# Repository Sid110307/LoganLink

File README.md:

# LoganLink

> Connected-Vehicle System for OBD-II supported cars

An OBD-II dongle plus a native Android app for older OBD-II petrol cars. The dongle reads the engine ECU over the K-line
(ISO 9141-2 / ISO 14230 KWP2000), measures the 12 V system (battery, cranking, charging), records driving events with an
accelerometer, logs locally and streams to the phone over Bluetooth LE. The phone supplies GPS, UI, trip history and alerts.

Developed on a 2008 Renault X90-platform sedan with the K7M 1.6.

## Repository

| Path | Contents |
| ------ | ---------- |
| `firmware/` | ESP-IDF v5.3 C firmware |
| `android/` | Android app |
| `hardware/` | PCB and BOM |
| `mechanical/` | Enclosure and print stuff |

## Features

- [x] QR card pairing with the dongle
- [x] Owner + up to 3 drivers with roles
- [x] Live RPM, speed, coolant, MAP, throttle, load, trims, battery, etc.
- [x] Full-screen Drive Mode
- [x] Floating car panel over Maps
- [x] Route map for every trip
- [x] Driving score from harsh braking, acceleration and idling
- [x] Trip summary notifications
- [x] Fuel consumption that self-calibrates with each fill-up
- [x] Fuel log and cost history
- [x] Alerts for overheating, charging faults, overvoltage, etc.
- [x] Charging system check
- [x] Battery health from cranking voltage
- [x] Service reminders by km and time
- [x] Odometer kept up to date by trips
- [x] VIN read and decoded (maker, model year)
- [x] Automatic protocol detection for K-line cars
- [x] Battery voltage calibration
- [x] Offline dongle logging
- [x] GPS speed when the car doesn't report it
- [x] RPM from alternator ripple fallback
- [x] Firmware updates over BT
- [x] Status LED for standby and driving
- [x] Low-power parked mode with hibernation
- [ ] Manufacturer data blocks for older ECUs
- [ ] Fuel level
- [ ] Ignition sensing
- [ ] Multiple cars in one app
- [ ] Home-screen widgets for battery, fuel and last trip
- [ ] "Where is my car" with Google Assistant
- [ ] Freeze frame data for fault codes
- [ ] Idle and fuel-trim adaptation resets
- [ ] Actuator tests: fan, fuel pump, A/C clutch, injectors
- [ ] Android Auto status cards
- [ ] CAN support

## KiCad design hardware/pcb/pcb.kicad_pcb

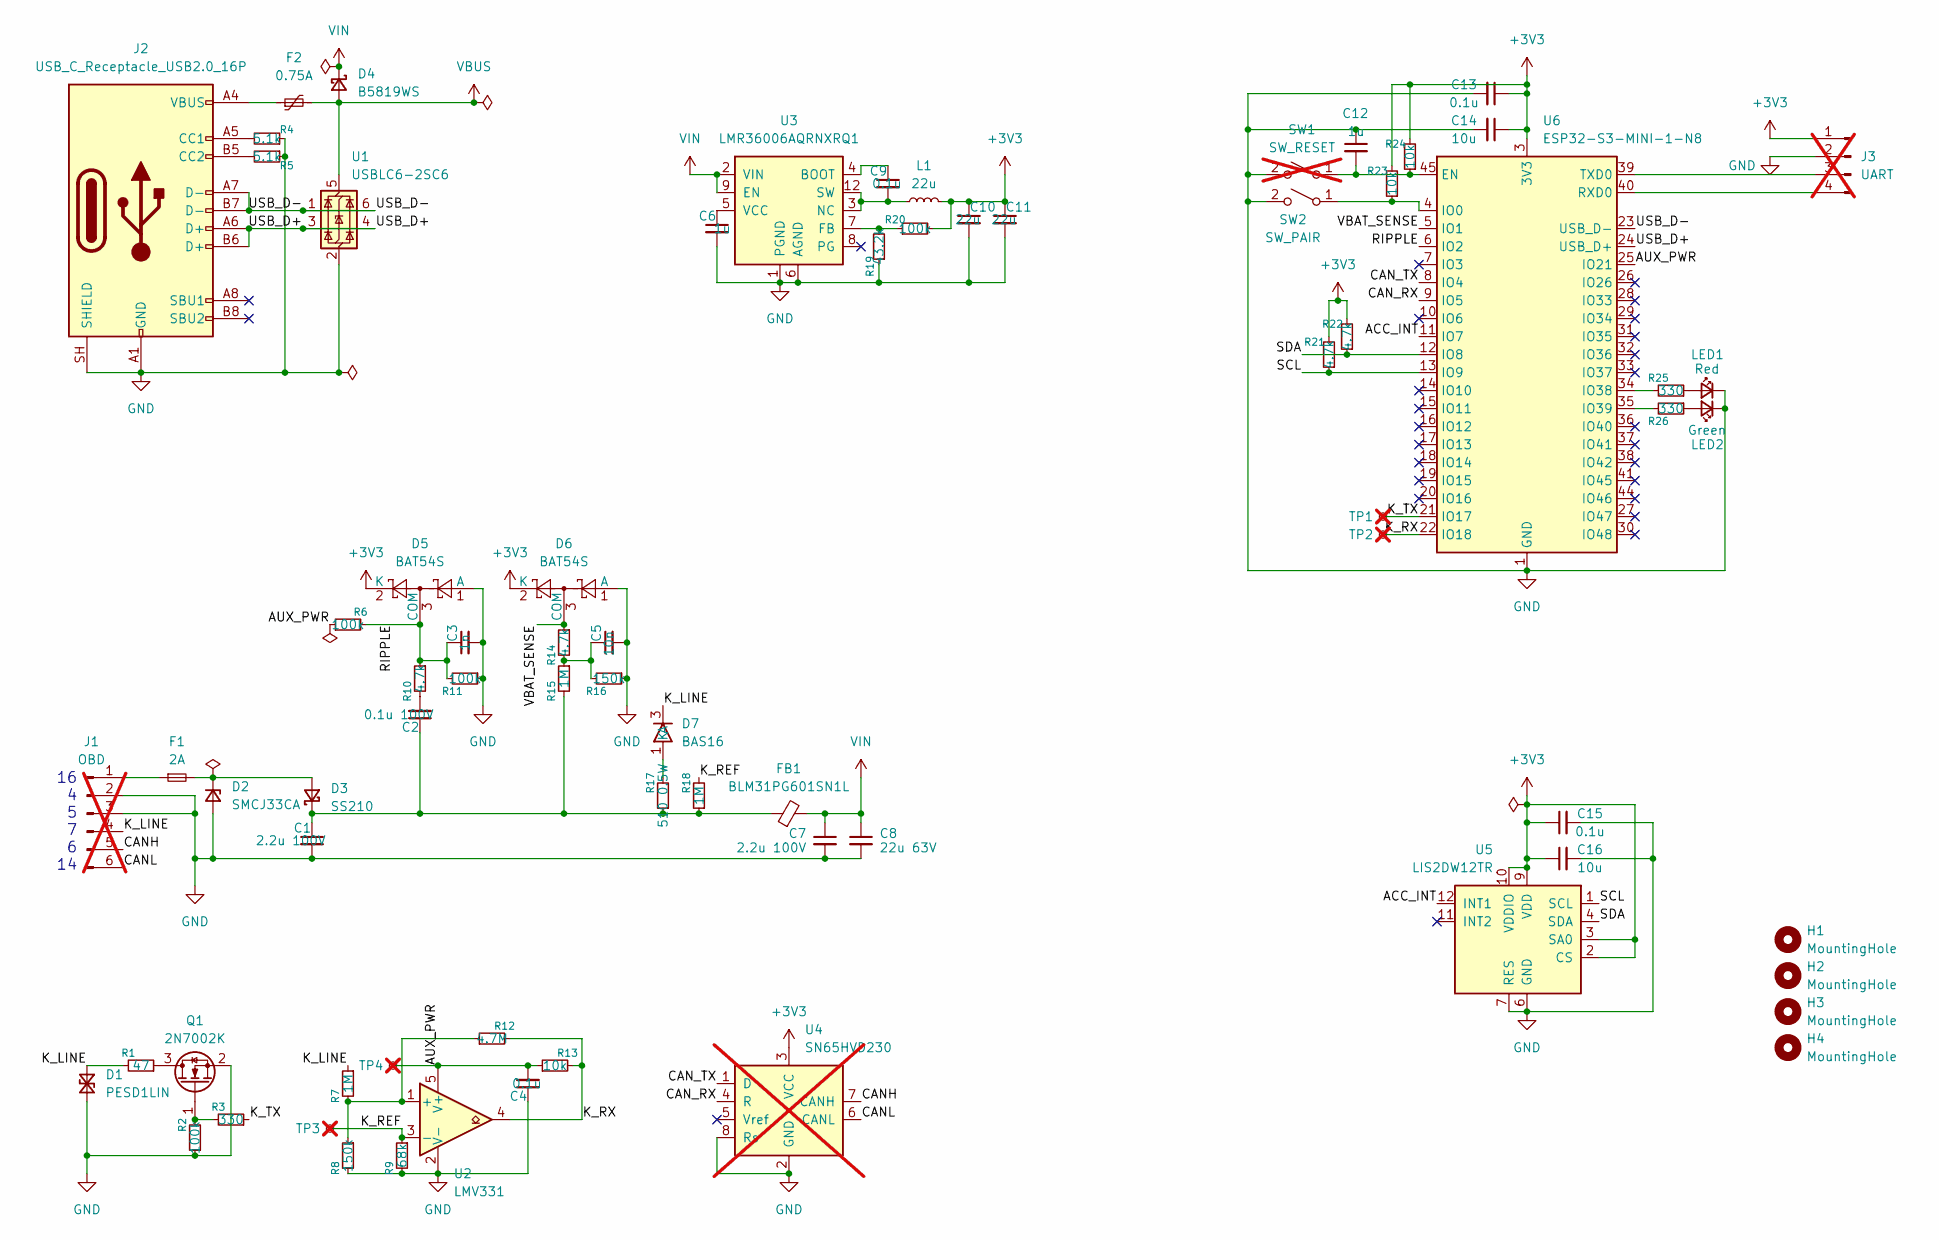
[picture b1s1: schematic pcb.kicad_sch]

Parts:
C1, C7: 2.2u 100V; C_1206_3216Metric; MPN CL31B225KCHSNNE
C2: 0.1u 100V; C_0603_1608Metric; MPN GRM188R72A104KA35D
C3: 1n; C_0402_1005Metric; MPN GRM1555C1H102JA01D
C4, C9, C13, C15: 0.1u; C_0402_1005Metric; MPN GCM155R71H104KE02D
C5: 10n; C_0402_1005Metric; MPN CL05B103KB5VPNC
C6, C12: 1u; C_0402_1005Metric; MPN GRT155R61E105KE01D
C8: 22u 63V; CP_Elec_6.3x5.8; MPN UCD1J220MCL1GS
C10, C11: 22u; C_1206_3216Metric; MPN GRM31CR61C226KE15L
C14, C16: 10u; C_0603_1608Metric; MPN GRM188R61A106ME69D
D1: PESD1LIN; D_SOD-323; MPN PESD1LIN-SL
D2: SMCJ33CA; D_SMC; MPN SMCJ33CA-13-F
D3: SS210; D_SMA; MPN SS210-HF
D4: B5819WS; D_SOD-323F; MPN B5819WS
D5, D6: BAT54S; SOT-23; MPN BAT54S
D7: BAS16; SOT-23; MPN BAS16
F1: 2A; Fuse_1206_3216Metric; MPN SF-1206FP200-2
F2: 0.75A; Fuse_1206_3216Metric; MPN MF-NSMF075-2
FB1: BLM31PG601SN1L; L_1206_3216Metric; MPN BLM31PG601SN1L
H1, H2, H3, H4: MountingHole; MountingHole_2.2mm_M2
J1: OBD; PinHeader_1x06_P2.54mm_Vertical; not fitted
J2: USB_C_Receptacle_USB2.0_16P; USB_C_Receptacle_GCT_USB4105-xx-A_16P_TopMnt_Horizontal; MPN USB4105-GF-A
J3: UART; PinHeader_1x04_P2.54mm_Vertical; not fitted
L1: 22u; L_Bourns-SRN4018; MPN SRN4018-220M
LED1: Red; LED_0603_1608Metric; MPN APT1608EC
LED2: Green; LED_0603_1608Metric; MPN APT1608SGC
Q1: 2N7002K; SOT-23; MPN 2N7002K-7
R1: 47; R_0603_1608Metric; MPN RC0603FR-0747RL
R2, R6, R11, R20: 100k; R_0402_1005Metric; MPN RC0402FR-07100KL
R3, R25, R26: 330; R_0402_1005Metric; MPN RC0402FR-07330RL
R4, R5: 5.1k; R_0402_1005Metric; MPN RC0402FR-075K1L
R7, R15, R18: 1M; R_0603_1608Metric; MPN RE0603DRE071ML
R8, R16: 150k; R_0603_1608Metric; MPN RT0603DRE07150KL
R9: 68k; R_0603_1608Metric; MPN RT0603DRE0768KL
R10, R14, R21, R22: 4.7k; R_0402_1005Metric; MPN RC0402FR-074K7L
R12: 4.7M; R_0402_1005Metric; MPN RC0402FR-074M7L
R13, R23, R24: 10k; R_0402_1005Metric; MPN RC0402FR-0710KL
R17: 510 0.5W; R_1206_3216Metric; MPN CRCW1206510RFKEAHP
R19: 43.2k; R_0402_1005Metric; MPN RC0402FR-0743K2L
SW1: SW_RESET; SW_SPST_B3U-1000P; MPN B3U-1100P-B; not fitted
SW2: SW_PAIR; SW_SPST_B3U-1000P; MPN B3U-1100P-B
TP1, TP2, TP3, TP4: TestPoint_Small; TestPoint_Pad_D1.0mm; not fitted
U1: USBLC6-2SC6; SOT-23-6; MPN USBLC6-2SC6
U2: LMV331; SOT-23-5; MPN LMV331IDBVR
U3: LMR36006AQRNXRQ1; TI_RNX0012A; MPN LMR36006AQRNXRQ1
U4: SN65HVD230; SOIC-8_3.9x4.9mm_P1.27mm; MPN SN65HVD230QDRQ1; not fitted
U5: LIS2DW12TR; LGA-12_2x2mm_P0.5mm; MPN LIS2DW12TR
U6: ESP32-S3-MINI-1-N8; ESP32-S2-MINI-1; MPN ESP32-S3-MINI-1-N8

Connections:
+3V3: C10.1, C11.1, C13.1, C14.1, C15.1, C16.1, D5.2 (K), D6.2 (K), J3.1, L1.2, R20.2, R21.2, R22.2, R23.2, R24.2, U4.3 (VCC), U5.2 (CS), U5.3 (SA0), U5.9 (VDD), U5.10 (VDDIO), U6.3 (3V3)
/ACC_INT: U5.12 (INT1), U6.11 (IO7)
/AUX_PWR: C4.2, R6.1, R13.1, TP4.1 (1_1), U2.5 (V+), U6.25 (IO21)
/CANH: J1.5, U4.7 (CANH)
/CANL: J1.6, U4.6 (CANL)
/CAN_RX: U4.4 (R), U6.9 (IO5)
/CAN_TX: U4.1 (D), U6.8 (IO4)
/K_LINE: D1.1 (A1), D7.3 (K), J1.4, R1.2, R7.1
/K_REF: R9.1, R18.2, TP3.1 (1_1), U2.3 (-)
/K_RX: R12.2, R13.2, TP2.1 (1_1), U2.4, U6.22 (IO18)
/K_TX: R3.1, TP1.1 (1_1), U6.21 (IO17)
/RIPPLE: C3.1, D5.3 (COM), R6.2, R10.1, R11.2, U6.6 (IO2)
/SCL: R21.1, U5.1 (SCL), U6.13 (IO9)
/SDA: R22.1, U5.4 (SDA), U6.12 (IO8)
/USB_D+: J2.A6 (D+), J2.B6 (D+), U1.3 (I/O2), U1.4 (I/O2), U6.24 (USB_D+)
/USB_D-: J2.A7 (D-), J2.B7 (D-), U1.1 (I/O1), U1.6 (I/O1), U6.23 (USB_D-)
/VBAT_SENSE: D6.3 (COM), R14.1, U6.5 (IO1)
GND: C1.2, C3.2, C4.1, C5.2, C6.2, C7.2, C8.2, C10.2, C11.2, C12.1, C13.2, C14.2, C15.2, C16.2, D1.2 (A2), D2.2 (A), D5.1 (A), D6.1 (A), J1.2, J1.3, J2.A1 (GND), J2.A12 (GND), J2.B1 (GND), J2.B12 (GND), J2.SH (SHIELD), J3.2, LED1.1 (K), LED2.1 (K), Q1.2 (S), R2.1, R4.1, R5.1, R8.2, R9.2, R11.1, R16.1, R19.1, SW1.2 (B), SW2.2 (B), U1.2 (GND), U2.2 (V-), U3.1 (PGND), U3.6 (AGND), U3.11 (PGND), U4.2 (GND), U4.8 (Rs), U5.6 (GND), U5.7 (RES), U5.8 (GND), U6.1 (GND), U6.2 (GND), U6.42 (GND), U6.43 (GND), U6.46 (GND), U6.47 (GND), U6.48 (GND), U6.49 (GND), U6.50 (GND), U6.51 (GND), U6.52 (GND), U6.53 (GND), U6.54 (GND), U6.55 (GND), U6.56 (GND), U6.57 (GND), U6.58 (GND), U6.59 (GND), U6.60 (GND), U6.61 (GND), U6.62 (GND), U6.63 (GND), U6.64 (GND), U6.65 (GND)
unnamed: C2.2, R10.2
unnamed: C5.1, R14.2, R15.1, R16.2
unnamed: D2.1 (K), D3.2 (A), F1.2
unnamed: C1.1, C2.1, D3.1 (K), FB1.1, R15.2, R17.1, R18.1
unnamed: D7.1 (A), R17.2
unnamed: F2.1, J2.A4 (VBUS), J2.A9 (VBUS), J2.B4 (VBUS), J2.B9 (VBUS)
unnamed: F1.1, J1.1
unnamed: J2.A5 (CC1), R4.2
unnamed: J2.B5 (CC2), R5.2
unnamed: J3.3, U6.39 (TXD0)
unnamed: J3.4, U6.40 (RXD0)
unnamed: LED1.2 (A), R25.1
unnamed: LED2.2 (A), R26.1
unnamed: Q1.3 (D), R1.1
unnamed: Q1.1 (G), R2.2, R3.2
unnamed: C12.2, R24.1, SW1.1 (A), U6.45 (EN)
unnamed: R23.1, SW2.1 (A), U6.4 (IO0)
unnamed: R7.2, R8.1, R12.1, U2.1 (+)
unnamed: C9.1, U3.4 (BOOT)
unnamed: R19.2, R20.1, U3.7 (FB)
unnamed: C9.2, L1.1, U3.3 (NC), U3.12 (SW)
unnamed: C6.1, U3.5 (VCC)
unnamed: R25.2, U6.34 (IO38)
unnamed: R26.2, U6.35 (IO39)
VBUS: D4.2 (A), F2.2, U1.5 (VBUS)
VIN: C7.1, C8.1, D4.1 (K), FB1.2, U3.2 (VIN), U3.9 (EN), U3.10 (VIN)

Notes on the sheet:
16 4 5 7 6 14

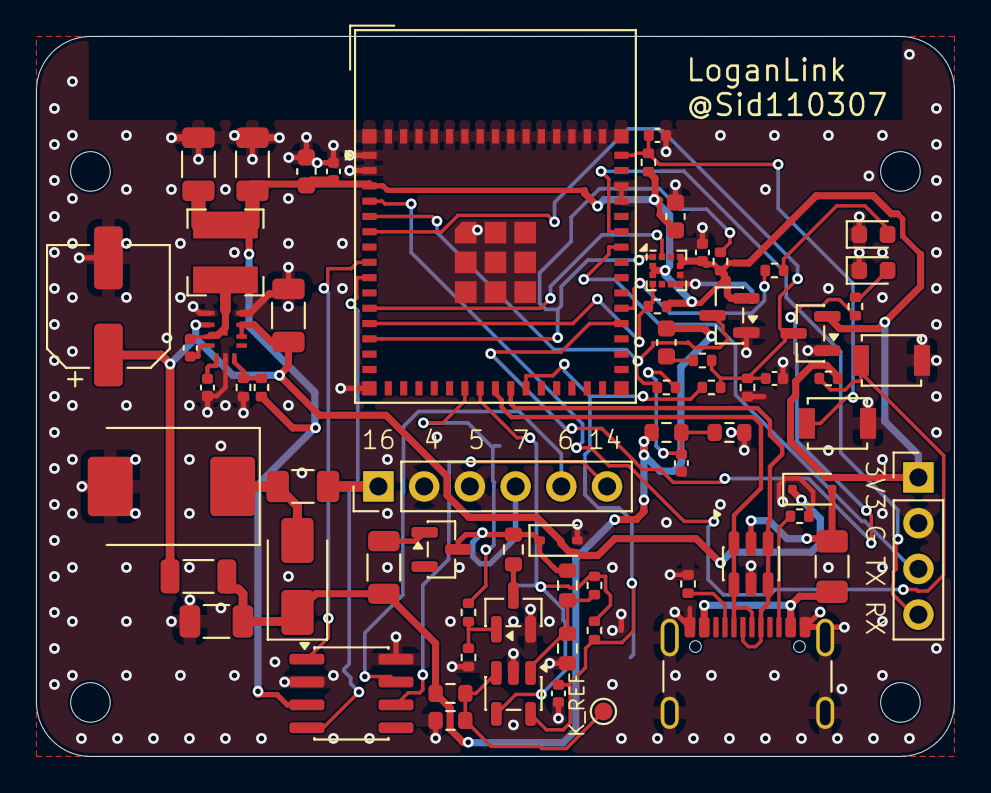
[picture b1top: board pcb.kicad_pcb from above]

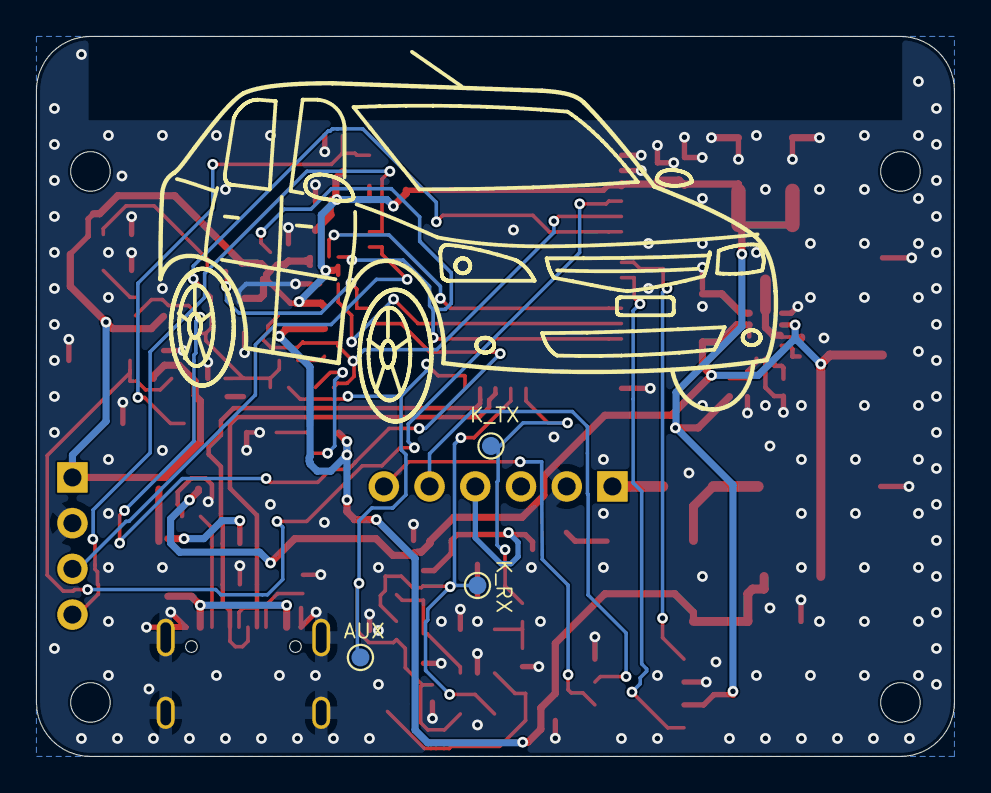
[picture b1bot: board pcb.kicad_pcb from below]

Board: 2 copper layers, 51.0 x 40.0 mm, 75 parts (3 on the bottom side), 44 nets.

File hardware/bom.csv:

"Sl No.","Designator","Description","Qty","MPN","DNP","Footprint","Value"
"1","C1,C7","MLCC 2.2uF 100V X7R 1206","2","CL31B225KCHSNNE","","Capacitor_SMD:C_1206_3216Metric","2.2u 100V"
"2","C2","MLCC 100nF 100V X7R 0603","1","GRM188R72A104KA35D","","Capacitor_SMD:C_0603_1608Metric","0.1u 100V"
"3","C3","MLCC 1nF 50V C0G 0402","1","GRM1555C1H102JA01D","","Capacitor_SMD:C_0402_1005Metric","1n"
"4","C4,C9,C13,C15","MLCC 100nF 50V X7R 0402","4","GCM155R71H104KE02D","","Capacitor_SMD:C_0402_1005Metric","0.1u"
"5","C5","MLCC 10nF 50V X7R 0402","1","CL05B103KB5VPNC","","Capacitor_SMD:C_0402_1005Metric","10n"
"6","C6,C12","MLCC 1uF 25V X5R 0402","2","GRT155R61E105KE01D","","Capacitor_SMD:C_0402_1005Metric","1u"
"7","C8","Aluminium electrolytic 22uF 63V SMD 6.3x7.7 (6.3 mm land pattern)","1","UCD1J220MCL1GS","","Capacitor_SMD:CP_Elec_6.3x5.8","22u 63V"
"8","C10,C11","MLCC 22uF 16V X5R 1206","2","GRM31CR61C226KE15L","","Capacitor_SMD:C_1206_3216Metric","22u"
"9","C14,C16","MLCC 10uF 10V X5R 0603","2","GRM188R61A106ME69D","","Capacitor_SMD:C_0603_1608Metric","10u"
"10","D1","ESD protection diode LIN bus SOD-323","1","PESD1LIN-SL","","Diode_SMD:D_SOD-323","PESD1LIN"
"11","D2","TVS diode bidirectional 33V standoff 1500W SMC","1","SMCJ33CA-13-F","","Diode_SMD:D_SMC","SMCJ33CA"
"12","D3","Schottky diode 100V 2A SMA","1","SS210-HF","","Diode_SMD:D_SMA","SS210"
"13","D4","Schottky diode 40V 1A SOD-323","1","B5819WS","","Diode_SMD:D_SOD-323F","B5819WS"
"14","D5,D6","Dual Schottky diode series 30V SOT-23","2","BAT54S","","Package_TO_SOT_SMD:SOT-23","BAT54S"
"15","D7","Switching diode 100V SOT-23","1","BAS16","","Package_TO_SOT_SMD:SOT-23","BAS16"
"16","F1","Fuse fast 2A 63V 1206","1","SF-1206FP200-2","","Fuse:Fuse_1206_3216Metric","2A"
"17","F2","PTC resettable fuse 0.75A hold 6V 1206","1","MF-NSMF075-2","","Fuse:Fuse_1206_3216Metric","0.75A"
"18","FB1","Ferrite bead 600R at 100MHz 1206","1","BLM31PG601SN1L","","Inductor_SMD:L_1206_3216Metric","BLM31PG601SN1L"
"19","J1","OBD wire pads (not assembled)","1","-","DNP","Connector_PinHeader_2.54mm:PinHeader_1x06_P2.54mm_Vertical","OBD"
"20","J2","USB Type-C receptacle USB2.0 16P","1","USB4105-GF-A","","Connector_USB:USB_C_Receptacle_GCT_USB4105-xx-A_16P_TopMnt_Horizontal","USB_C_Receptacle_USB2.0_16P"
"21","J3","UART console pads (not assembled)","1","-","DNP","Connector_PinHeader_2.54mm:PinHeader_1x04_P2.54mm_Vertical","UART"
"22","L1","Power inductor 22uH shielded 4x4 Isat 0.95A","1","SRN4018-220M","","Inductor_SMD:L_Bourns-SRN4018","22u"
"23","LED1","LED red 0603","1","APT1608EC","","LED_SMD:LED_0603_1608Metric","Red"
"24","LED2","LED green 0603","1","APT1608SGC","","LED_SMD:LED_0603_1608Metric","Green"
"25","Q1","N-MOSFET 60V 0.3A SOT-23","1","2N7002K-7","","Package_TO_SOT_SMD:SOT-23","2N7002K"
"26","R1","Chip resistor 47R 1% 1/10W 0603","1","RC0603FR-0747RL","","Resistor_SMD:R_0603_1608Metric","47"
"27","R2,R6,R11,R20","Chip resistor 100k 1% 1/16W 0402","4","RC0402FR-07100KL","","Resistor_SMD:R_0402_1005Metric","100k"
"28","R3,R25,R26","Chip resistor 330R 1% 1/16W 0402","3","RC0402FR-07330RL","","Resistor_SMD:R_0402_1005Metric","330"
"29","R4,R5","Chip resistor 5.1k 1% 1/16W 0402","2","RC0402FR-075K1L","","Resistor_SMD:R_0402_1005Metric","5.1k"
"30","R7,R15,R18","Chip resistor 1M 0.5% 1/10W 0603","3","RE0603DRE071ML","","Resistor_SMD:R_0603_1608Metric","1M"
"31","R8,R16","Chip resistor 150k 0.5% 1/10W 0603","2","RT0603DRE07150KL","","Resistor_SMD:R_0603_1608Metric","150k"
"32","R9","Chip resistor 68k 0.5% 1/10W 0603","1","RT0603DRE0768KL","","Resistor_SMD:R_0603_1608Metric","68k"
"33","R10,R14,R21,R22","Chip resistor 4.7k 1% 1/16W 0402","4","RC0402FR-074K7L","","Resistor_SMD:R_0402_1005Metric","4.7k"
"34","R12","Chip resistor 4.7M 1% 1/16W 0402","1","RC0402FR-074M7L","","Resistor_SMD:R_0402_1005Metric","4.7M"
"35","R13,R23,R24","Chip resistor 10k 1% 1/16W 0402","3","RC0402FR-0710KL","","Resistor_SMD:R_0402_1005Metric","10k"
"36","R17","Chip resistor 510R 1% 0.5W 1206 anti-surge","1","CRCW1206510RFKEAHP","","Resistor_SMD:R_1206_3216Metric","510 0.5W"
"37","R19","Chip resistor 43.2k 1% 1/16W 0402","1","RC0402FR-0743K2L","","Resistor_SMD:R_0402_1005Metric","43.2k"
"38","SW1","Tactile switch SPST-NO SMD (reset; not assembled)","1","B3U-1100P-B","DNP","Button_Switch_SMD:SW_SPST_B3U-1000P","SW_RESET"
"39","SW2","Tactile switch SPST-NO SMD 2-pin","1","B3U-1100P-B","","Button_Switch_SMD:SW_SPST_B3U-1000P","SW_PAIR"
"40","TP1,TP2,TP3,TP4","Test pad (not assembled)","4","-","DNP","TestPoint:TestPoint_Pad_D1.0mm","TestPoint_Small"
"41","U1","USB ESD protection diode array SOT-23-6","1","USBLC6-2SC6","","Package_TO_SOT_SMD:SOT-23-6","USBLC6-2SC6"
"42","U2","Comparator low-voltage open-drain SOT-23-5","1","LMV331IDBVR","","Package_TO_SOT_SMD:SOT-23-5","LMV331"
"43","U3","Buck converter 60V 0.6A 3.3V VQFN-HR-12","1","LMR36006AQRNXRQ1","","loganlink:TI_RNX0012A","LMR36006AQRNXRQ1"
"44","U4","CAN transceiver 3.3V SOIC-8 (CAN cars only)","1","SN65HVD230QDRQ1","DNP","Package_SO:SOIC-8_3.9x4.9mm_P1.27mm","SN65HVD230"
"45","U5","Accelerometer 3-axis I2C LGA-12","1","LIS2DW12TR","","Package_LGA:LGA-12_2x2mm_P0.5mm","LIS2DW12TR"
"46","U6","Wi-Fi + BLE module ESP32-S3 8MB flash","1","ESP32-S3-MINI-1-N8","","RF_Module:ESP32-S2-MINI-1","ESP32-S3-MINI-1-N8"

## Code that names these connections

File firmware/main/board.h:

#pragma once
#include "driver/gpio.h"
#include "hal/adc_types.h"

#define FW_VERSION_MAJOR 1
#define FW_VERSION_MINOR 1
#define FW_VERSION_PATCH 0
#define HW_REVISION      'B'

#define PIN_BTN_PAIR       GPIO_NUM_0
#define PIN_LED_R          GPIO_NUM_38
#define PIN_LED_G          GPIO_NUM_39

#define ADC_CH_VBAT_DC     ADC_CHANNEL_0
#define ADC_CH_VBAT_AC     ADC_CHANNEL_1

#define PIN_CAN_TX         GPIO_NUM_4
#define PIN_CAN_RX         GPIO_NUM_5
#define PIN_IGN_SENSE_N    GPIO_NUM_6
#define PIN_K_TX           GPIO_NUM_17
#define PIN_K_RX           GPIO_NUM_18
#define K_UART             UART_NUM_1

#define PIN_AUX_PWR        GPIO_NUM_21

#define PIN_ACC_WAKE_INT   GPIO_NUM_7
#define I2C_PORT           I2C_NUM_0
#define PIN_I2C_SDA        GPIO_NUM_8
#define PIN_I2C_SCL        GPIO_NUM_9
#define LIS2DW12_ADDR      0x19

#define VBAT_DIV_NUM       1150
#define VBAT_DIV_DEN       150

#define ENGINE_DISPLACEMENT_L   1.598f
#define FUEL_DENSITY_KG_L       0.745f
#define AFR_STOICH              14.7f
